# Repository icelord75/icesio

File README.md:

# iceSIO
iceSIO replacement board for CASIO 3208 modules (CA-53, CA-506 watches)

## Hardware
* MCU: Microchip **PIC16F19197** - 8bit MCU, 56kB flash, 4K RAM, 256b EEPROM
* EEPROM: Microchip **24CW1280T-I/CS0668** - 16KB, WLCSP package
* Accelerometer: NXP **MMA8451QT** - 3-axis, 14-bit/8-bit digital accelerometer
* Compass: Honeywell **HMC5883L** or Isentek **IST8310** - 3-Axis Digital Compass
* Environment: BOSCH **BME280** - Digital humidity, pressure and temperature sensor
* LED:
  * ON Semiconductor **NCP5623CMUTBG** - Triple Output I2C Controlled RGB LED Driver
  * Songxin **SX-0402-RGB** - SMD fullcolor RGB SMD0404 LED
* Battery: **CR2016** -> CR2020 / CR2025 / CR2320 upgradable?

## Features
* TTL 19200bps UART for debug and evolution.
* RTCC for timekeeping.

## Pictures

## TODO Features
* Controls: 2 side buttons + 4*4 keypad
* Timekeeping: Home and World time with automatic DST and assisted calibration
* Perpetual calendar: up to year 2199
* Calculator: Infix, Prefix or Reverse Polish notation (configurable), -9.999999*1099 — +9.9999999*1099 (visual 8 digits mantissa)
* Alarm: 5 daily alarms + 5 weekly alarms + hour signal
* Start/Stop watch: 5 stopwatches up to 23:59:59.59 with 0.01 second resolution
* Timer: 5 countdown timers up to 99:59:59 with 1 second resolution
* Signal: Ring Tone Text Transfer Language (RTTTL) alarm and timer signals
* Minute repeater: audibly chimes the hours and minutes.
* BackLight: full RGB backlight, alarm and timers (configured separately) lights
* Sun: Sunrise and Sunset (Latitude presets + timezone)
* Moon: Precise Moon phase (icon and date)
* Equation of time
* Accelerometer:
  * tap-sensing control
  * tilt sensor
  * speedometer
  * continuous accelerometer
  * 0-100kmh acceleration/deceleration
* Compass:
  * Regular compass
  * Angle finder
* Enviromental sensor:
  * Current temperature (C°/F°)
  * Tranding temperature - hour/12h/24h
  * Current Humidity (%)
  * Tranding humidity - hour/12h/24h
  * Current Barometer (hPA, mBar, at, atm, Torr, mmHg, PSI, inHg)
  * Tranding barometer - hour/12h/24h

## Related Projects
[goodwatch](https://github.com/travisgoodspeed/goodwatch) replacement circuit board for the Casio 3208 module, used in the Casio CA-53W and CA-506 calculator watches.

[Pluto](https://github.com/carrotIndustries/pluto) is a replacement PCB for the Casio F-91W that is also based on an MSP430.

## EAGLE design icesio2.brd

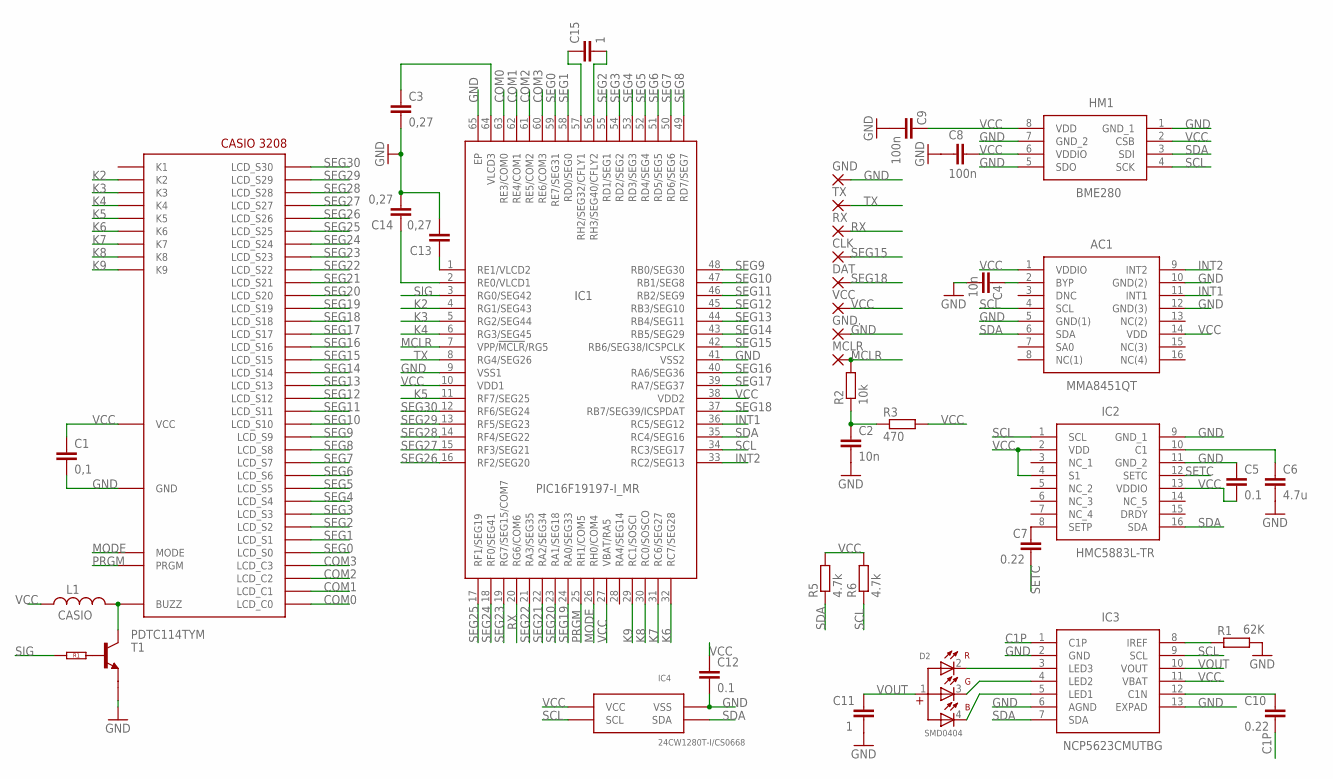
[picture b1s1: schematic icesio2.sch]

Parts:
AC1: MMA8451QT; PQFN50P300X300X100-16N
C1: 0,1; RESC0402_L
C2, C4: 10n; RESC0402_L
C3, C13, C14: 0,27; RESC0402_L
C5, C12: 0.1; RESC0402_L
C6: 4.7u; RESC0402_L
C7, C10: 0.22; RESC0402_L
C8, C9: 100n; RESC0402_L
C11, C15: 1; RESC0402_L
CLK: WIREPADSMD1,27-254; SMD1,27-2,54
D2: SMD0404; WL-SFCC_0404
DAT: WIREPADSMD1,27-254; SMD1,27-2,54
GND, GND.: WIREPADSMD1,27-254; SMD1,27-2,54
HM1: BME280
IC1: PIC16F19197-I_MR; QFN50P900X900X100-65N
IC2: HMC5883L-TR; 16-PIN-LPCC
IC3: NCP5623CMUTBG; NCP5623BMUTBG
IC4: 24CW1280T-I/CS0668; CSP
L1: CASIO; L4516C
MCLR: WIREPADSMD1,27-254; SMD1,27-2,54
R1: 62K; R0402
R2: 10k; R0402
R3: 470; R0402
R5, R6: 4.7k; R0402
RX: WIREPADSMD1,27-254; SMD1,27-2,54
T1: PDTC114TYM; SOT883(B)
TX: WIREPADSMD1,27-254; SMD1,27-2,54
U$1: CASIO3208
VCC: WIREPADSMD1,27-254; SMD1,27-2,54

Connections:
BUZ: L1.2, T1.3 (C), U$1.BUZZ
BYP: AC1.2 (BYP), C4.1
C1: C6.1, IC2.10 (C1)
C1P: C10.2, IC3.1 (C1P)
CFLY1: C15.1, IC1.57 (RH2/SEG32/CFLY1)
CFLY2: C15.2, IC1.56 (RH3/SEG40/CFLY2)
COM0: IC1.63 (RE3/COM0), U$1.LCD1 (LCD_C0)
COM1: IC1.62 (RE4/COM1), U$1.LCD2 (LCD_C1)
COM2: IC1.61 (RE5/COM2), U$1.LCD3 (LCD_C2)
COM3: IC1.60 (RE6/COM3), U$1.LCD4 (LCD_C3)
GND: AC1.5 (GND(1)), AC1.10 (GND(2)), AC1.12 (GND(3)), C1.2, C2.2, C3.2, C4.2, C5.1, C6.2, C8.2, C9.2, C11.2, C12.2, C13.2, C14.2, GND.1, GND..1, HM1.1 (GND_1), HM1.5 (SDO), HM1.7 (GND_2), IC1.9 (VSS1), IC1.41 (VSS2), IC1.65 (EP), IC2.9 (GND_1), IC2.11 (GND_2), IC3.2 (GND), IC3.6 (AGND), IC3.13 (EXPAD), IC4.VSS, R1.2, T1.2 (E), U$1.GND
INT1: AC1.11 (INT1), IC1.36 (RC5/SEG12)
INT2: AC1.9 (INT2), IC1.33 (RC2/SEG13)
K2: IC1.4 (RG1/SEG43), U$1.K2
K3: IC1.5 (RG2/SEG44), U$1.K3
K4: IC1.6 (RG3/SEG45), U$1.K4
K5: IC1.11 (RF7/SEG25), U$1.K5
K6: IC1.32 (RC7/SEG28), U$1.K6
K7: IC1.31 (RC6/SEG27), U$1.K7
K8: IC1.30 (RC0/SOSCO), U$1.K8
K9: IC1.29 (RC1/SOSCI), U$1.K9
MCLR: IC1.7 (VPP/!MCLR!/RG5), MCLR.1, R2.2
MCLRVCC: C2.1, R2.1, R3.1
MODE: IC1.26 (RH0/COM4), U$1.MODE
unnamed: D2.2 (R), IC3.3 (LED3)
unnamed: C7.1, IC2.8 (SETP)
unnamed: D2.3 (G), IC3.4 (LED2)
unnamed: D2.4 (B), IC3.5 (LED1)
unnamed: IC3.8 (IREF), R1.1
unnamed: C10.1, IC3.12 (C1N)
PRGM: IC1.25 (RH1/COM5), U$1.PRGM
RX: IC1.20 (RG6/COM6), RX.1
SCL: AC1.4 (SCL), HM1.4 (SCK), IC1.34 (RC3/SEG17), IC2.1 (SCL), IC3.9 (SCL), IC4.SCL, R6.1
SDA: AC1.6 (SDA), HM1.3 (SDI), IC1.35 (RC4/SEG16), IC2.16 (SDA), IC3.7 (SDA), IC4.SDA, R5.1
SEG0: IC1.59 (RE7/SEG31), U$1.LCD5 (LCD_S0)
SEG1: IC1.58 (RD0/SEG0), U$1.LCD6 (LCD_S1)
SEG2: IC1.55 (RD1/SEG1), U$1.LCD7 (LCD_S2)
SEG3: IC1.54 (RD2/SEG2), U$1.LCD8 (LCD_S3)
SEG4: IC1.53 (RD3/SEG3), U$1.LCD9 (LCD_S4)
SEG5: IC1.52 (RD4/SEG4), U$1.LCD10 (LCD_S5)
SEG6: IC1.51 (RD5/SEG5), U$1.LCD11 (LCD_S6)
SEG7: IC1.50 (RD6/SEG6), U$1.LCD12 (LCD_S7)
SEG8: IC1.49 (RD7/SEG7), U$1.LCD13 (LCD_S8)
SEG9: IC1.48 (RB0/SEG30), U$1.LCD14 (LCD_S9)
SEG10: IC1.47 (RB1/SEG8), U$1.LCD15 (LCD_S10)
SEG11: IC1.46 (RB2/SEG9), U$1.LCD16 (LCD_S11)
SEG12: IC1.45 (RB3/SEG10), U$1.LCD17 (LCD_S12)
SEG13: IC1.44 (RB4/SEG11), U$1.LCD18 (LCD_S13)
SEG14: IC1.43 (RB5/SEG29), U$1.LCD19 (LCD_S14)
SEG15: CLK.1, IC1.42 (RB6/SEG38/ICSPCLK), U$1.LCD20 (LCD_S15)
SEG16: IC1.40 (RA6/SEG36), U$1.LCD21 (LCD_S16)
SEG17: IC1.39 (RA7/SEG37), U$1.LCD22 (LCD_S17)
SEG18: DAT.1, IC1.37 (RB7/SEG39/ICSPDAT), U$1.LCD23 (LCD_S18)
SEG19: IC1.24 (RA0/SEG33), U$1.LCD24 (LCD_S19)
SEG20: IC1.23 (RA1/SEG18), U$1.LCD25 (LCD_S20)
SEG21: IC1.22 (RA2/SEG34), U$1.LCD26 (LCD_S21)
SEG22: IC1.21 (RA3/SEG35), U$1.LCD27 (LCD_S22)
SEG23: IC1.19 (RG7/SEG15/COM7), U$1.LCD28 (LCD_S23)
SEG24: IC1.18 (RF0/SEG41), U$1.LCD29 (LCD_S24)
SEG25: IC1.17 (RF1/SEG19), U$1.LCD30 (LCD_S25)
SEG26: IC1.16 (RF2/SEG20), U$1.LCD31 (LCD_S26)
SEG27: IC1.15 (RF3/SEG21), U$1.LCD32 (LCD_S27)
SEG28: IC1.14 (RF4/SEG22), U$1.LCD33 (LCD_S28)
SEG29: IC1.13 (RF5/SEG23), U$1.LCD34 (LCD_S29)
SEG30: IC1.12 (RF6/SEG24), U$1.LCD35 (LCD_S30)
SETC: C7.2, IC2.12 (SETC)
SIG: IC1.3 (RG0/SEG42), T1.1 (INPUT)
TX: IC1.8 (RG4/SEG26), TX.1
VCC: AC1.1 (VDDIO), AC1.14 (VDD), C1.1, C5.2, C8.1, C9.1, C12.1, HM1.2 (CSB), HM1.6 (VDDIO), HM1.8 (VDD), IC1.10 (VDD1), IC1.27 (VBAT/RA5), IC1.38 (VDD2), IC2.2 (VDD), IC2.4 (S1), IC2.13 (VDDIO), IC3.11 (VBAT), IC4.VCC, L1.1, R3.2, R5.2, R6.2, U$1.VCC, VCC.1
VLCD1: C14.1, IC1.2 (RE0/VLCD1)
VLCD2: C13.1, IC1.1 (RE1/VLCD2)
VLCD3: C3.1, IC1.64 (VLCD3)
VOUT: C11.1, D2.1, IC3.10 (VOUT)

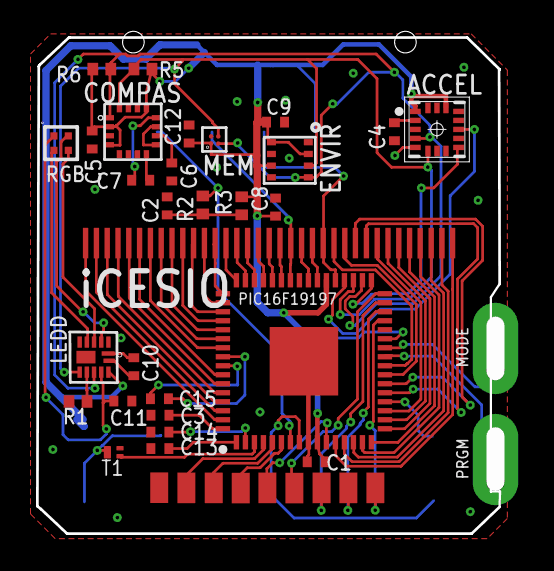
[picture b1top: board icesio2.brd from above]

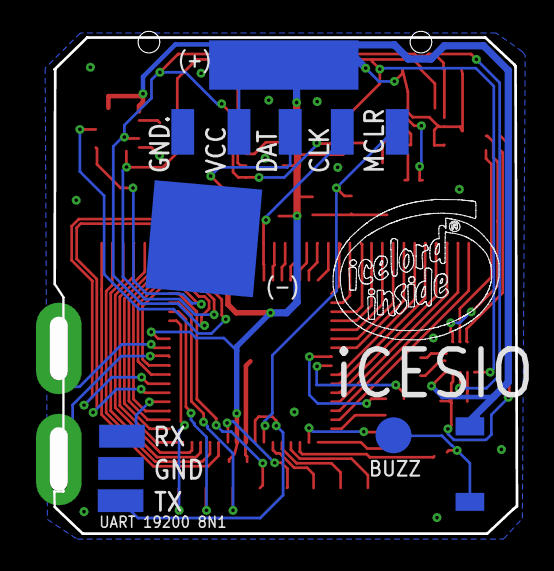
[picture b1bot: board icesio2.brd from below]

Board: 2 copper layers, 25.7 x 27.6 mm, 39 parts (10 on the bottom side), 73 nets.

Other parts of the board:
U$2: ICELORD_SMALL

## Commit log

2019-03-12 Upload hardware
2019-05-04 shematics
2019-05-04 adding png
2019-05-04 clean

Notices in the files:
parts and their libraries:
Wurth_Elektronik_Optoelectronics_rev18g: Copyright: Würth Elektronik
